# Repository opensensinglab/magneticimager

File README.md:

Magnetic Imaging Tile
======

Work-in-progress.  Please use at your own risk. <br>

This is a board intended to function as a "magnetic field camera", and visualize magnetic fields. 

### Version 3.0

The major advancement of v3.0 is a dramatic increase in the speed with which the tile data can be read out.  I have achieved ~2000 frames per second (fps), which allows visualizing even quickly varying fields (e.g. those in a 60Hz transformer, or a moving motor), but it's likely that the tile can achieve even higher framerates.  Version 3.0 reduces the size of the tile to an 8x8 grid of hall effect sensors (64 total), arrayed in a 4mm grid.  The boards should also still be tile-able, with up to 4 of the boards tileable with minimal borders to create a 16x16 array. 

For more information (and a video of the v3.0 tile in use), please see: 
https://hackaday.io/project/18518-iteration-8/log/91551-a-third-high-speed-magnetic-imager-tile-draft

### Version 2.0

Version 2.0 consists of an array of 12x12 hall effect sensors (144 total) that sense magnetic fields, arrayed in a 4mm grid.  Each sensor is connected to an array of analog switches, that allow an individual sensor to be addressed.  Read out is accomplished one magnetic "pixel" at a time, selecting a given hall sensor from the array, reading it's value (either using the internal ADC, or an external ADC), and repeating this process until the entire array has been read out.  

The current array is designed to be tile-able, with up to four of the boards (24x24 magnetic field sensors) arrayed together. 

The Arduino firmware has a framerate of approximately 10 frames per second, when the image data is streamed over the serial port and displayed using the Processing visualization.  The Raspberry Pi Python example achieves approximately 30fps.  The array itself is likely capable of much higher speeds, but one of the major limiting factors is currently the speed of the I2C I/O multiplexer (used to select which magnetometer to read from). 

For more information (and a video of the v2.0 tile in use), please see: 
https://hackaday.io/project/18518-iteration-8/log/64376-a-magnetic-imager-tile

# Open Source

This project is open source software and hardware, and is released under various open licenses.

# Disclaimer

**DISCLAIMER OF WARRANTIES AND LIMITATION OF LIABILITY.**

UNLESS OTHERWISE SEPARATELY UNDERTAKEN BY THE LICENSOR, TO THE EXTENT POSSIBLE, THE LICENSOR OFFERS THE LICENSED MATERIAL AS-IS AND AS-AVAILABLE, AND MAKES NO REPRESENTATIONS OR WARRANTIES OF ANY KIND CONCERNING THE LICENSED MATERIAL, WHETHER EXPRESS, IMPLIED, STATUTORY, OR OTHER. THIS INCLUDES, WITHOUT LIMITATION, WARRANTIES OF TITLE, MERCHANTABILITY, FITNESS FOR A PARTICULAR PURPOSE, NON-INFRINGEMENT, ABSENCE OF LATENT OR OTHER DEFECTS, ACCURACY, OR THE PRESENCE OR ABSENCE OF ERRORS, WHETHER OR NOT KNOWN OR DISCOVERABLE. WHERE DISCLAIMERS OF WARRANTIES ARE NOT ALLOWED IN FULL OR IN PART, THIS DISCLAIMER MAY NOT APPLY TO YOU.

TO THE EXTENT POSSIBLE, IN NO EVENT WILL THE LICENSOR BE LIABLE TO YOU ON ANY LEGAL THEORY (INCLUDING, WITHOUT LIMITATION, NEGLIGENCE) OR OTHERWISE FOR ANY DIRECT, SPECIAL, INDIRECT, INCIDENTAL, CONSEQUENTIAL, PUNITIVE, EXEMPLARY, OR OTHER LOSSES, COSTS, EXPENSES, OR DAMAGES ARISING OUT OF THIS PUBLIC LICENSE OR USE OF THE LICENSED MATERIAL, EVEN IF THE LICENSOR HAS BEEN ADVISED OF THE POSSIBILITY OF SUCH LOSSES, COSTS, EXPENSES, OR DAMAGES. WHERE A LIMITATION OF LIABILITY IS NOT ALLOWED IN FULL OR IN PART, THIS LIMITATION MAY NOT APPLY TO YOU.

THE DISCLAIMER OF WARRANTIES AND LIMITATION OF LIABILITY PROVIDED ABOVE SHALL BE INTERPRETED IN A MANNER THAT, TO THE EXTENT POSSIBLE, MOST CLOSELY APPROXIMATES AN ABSOLUTE DISCLAIMER AND WAIVER OF ALL LIABILITY.

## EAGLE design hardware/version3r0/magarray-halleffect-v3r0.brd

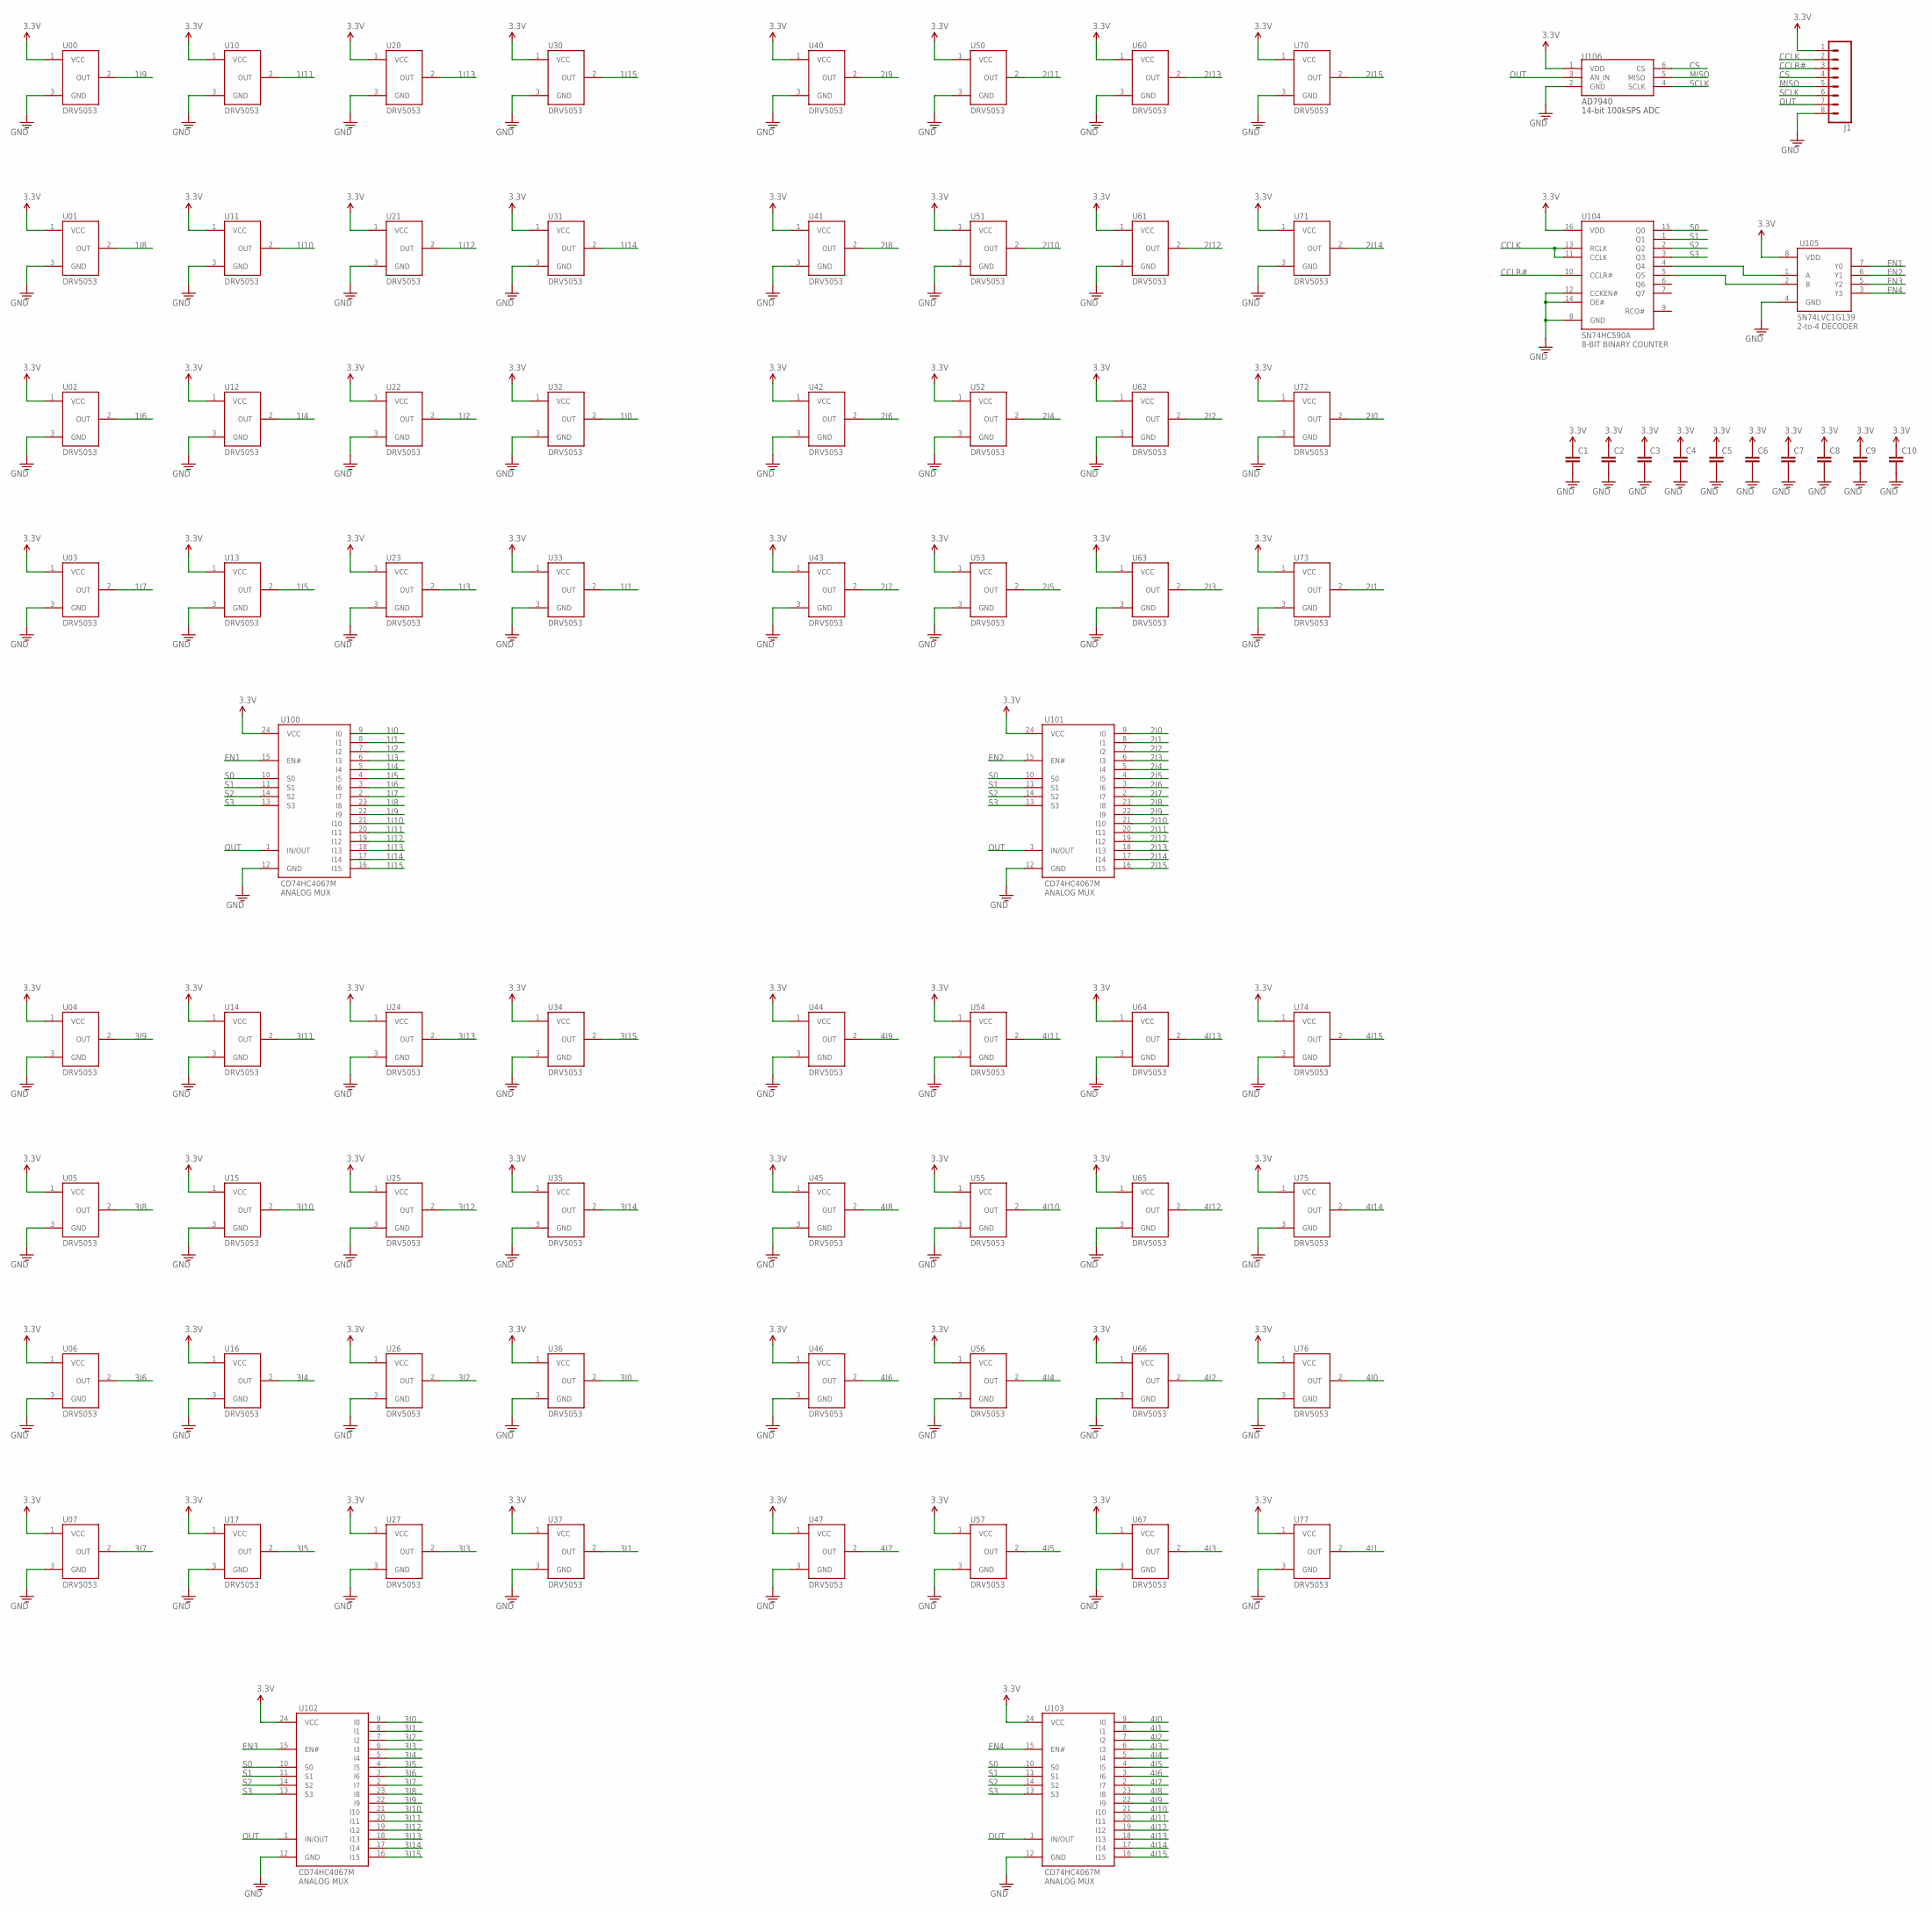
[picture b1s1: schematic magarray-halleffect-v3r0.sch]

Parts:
C1, C2, C3, C4, C5, C6, C7, C8, C9, C10: CAP0603; 0603
J1: CONN_08LOCK_NO_SILK; 1X08_LOCK_NO_SILK
U00, U01, U02, U03, U04, U05, U06, U07, U10, U11, U12, U13, U14, U15, U16, U17, U20, U21, U22, U23, U24, U25, U26, U27, U30, U31, U32, U33, U34, U35, U36, U37, U40, U41, U42, U43, U44, U45, U46, U47, U50, U51, U52, U53, U54, U55, U56, U57, U60, U61, U62, U63, U64, U65, U66, U67, U70, U71, U72, U73, U74, U75, U76, U77: DRV5053; SOT-23
U100, U101, U102, U103: CD74HC4067M; SOIC-24
U104: SN74HC509A; SO16
U105: SN74LVC1G139; SM8
U106: AD7940; SOT-23-6L

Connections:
1I0: U32.2 (OUT), U100.9 (I0)
1I1: U33.2 (OUT), U100.8 (I1)
1I2: U22.2 (OUT), U100.7 (I2)
1I3: U23.2 (OUT), U100.6 (I3)
1I4: U12.2 (OUT), U100.5 (I4)
1I5: U13.2 (OUT), U100.4 (I5)
1I6: U02.2 (OUT), U100.3 (I6)
1I7: U03.2 (OUT), U100.2 (I7)
1I8: U01.2 (OUT), U100.23 (I8)
1I9: U00.2 (OUT), U100.22 (I9)
1I10: U11.2 (OUT), U100.21 (I10)
1I11: U10.2 (OUT), U100.20 (I11)
1I12: U21.2 (OUT), U100.19 (I12)
1I13: U20.2 (OUT), U100.18 (I13)
1I14: U31.2 (OUT), U100.17 (I14)
1I15: U30.2 (OUT), U100.16 (I15)
2I0: U72.2 (OUT), U101.9 (I0)
2I1: U73.2 (OUT), U101.8 (I1)
2I2: U62.2 (OUT), U101.7 (I2)
2I3: U63.2 (OUT), U101.6 (I3)
2I4: U52.2 (OUT), U101.5 (I4)
2I5: U53.2 (OUT), U101.4 (I5)
2I6: U42.2 (OUT), U101.3 (I6)
2I7: U43.2 (OUT), U101.2 (I7)
2I8: U41.2 (OUT), U101.23 (I8)
2I9: U40.2 (OUT), U101.22 (I9)
2I10: U51.2 (OUT), U101.21 (I10)
2I11: U50.2 (OUT), U101.20 (I11)
2I12: U61.2 (OUT), U101.19 (I12)
2I13: U60.2 (OUT), U101.18 (I13)
2I14: U71.2 (OUT), U101.17 (I14)
2I15: U70.2 (OUT), U101.16 (I15)
3.3V: C1.1, C2.1, C3.1, C4.1, C5.1, C6.1, C7.1, C8.1, C9.1, C10.1, J1.1, U00.1 (VCC), U01.1 (VCC), U02.1 (VCC), U03.1 (VCC), U04.1 (VCC), U05.1 (VCC), U06.1 (VCC), U07.1 (VCC), U10.1 (VCC), U11.1 (VCC), U12.1 (VCC), U13.1 (VCC), U14.1 (VCC), U15.1 (VCC), U16.1 (VCC), U17.1 (VCC), U20.1 (VCC), U21.1 (VCC), U22.1 (VCC), U23.1 (VCC), U24.1 (VCC), U25.1 (VCC), U26.1 (VCC), U27.1 (VCC), U30.1 (VCC), U31.1 (VCC), U32.1 (VCC), U33.1 (VCC), U34.1 (VCC), U35.1 (VCC), U36.1 (VCC), U37.1 (VCC), U40.1 (VCC), U41.1 (VCC), U42.1 (VCC), U43.1 (VCC), U44.1 (VCC), U45.1 (VCC), U46.1 (VCC), U47.1 (VCC), U50.1 (VCC), U51.1 (VCC), U52.1 (VCC), U53.1 (VCC), U54.1 (VCC), U55.1 (VCC), U56.1 (VCC), U57.1 (VCC), U60.1 (VCC), U61.1 (VCC), U62.1 (VCC), U63.1 (VCC), U64.1 (VCC), U65.1 (VCC), U66.1 (VCC), U67.1 (VCC), U70.1 (VCC), U71.1 (VCC), U72.1 (VCC), U73.1 (VCC), U74.1 (VCC), U75.1 (VCC), U76.1 (VCC), U77.1 (VCC), U100.24 (VCC), U101.24 (VCC), U102.24 (VCC), U103.24 (VCC), U104.16 (VDD), U105.8 (VDD), U106.1 (VDD)
3I0: U36.2 (OUT), U102.9 (I0)
3I1: U37.2 (OUT), U102.8 (I1)
3I2: U26.2 (OUT), U102.7 (I2)
3I3: U27.2 (OUT), U102.6 (I3)
3I4: U16.2 (OUT), U102.5 (I4)
3I5: U17.2 (OUT), U102.4 (I5)
3I6: U06.2 (OUT), U102.3 (I6)
3I7: U07.2 (OUT), U102.2 (I7)
3I8: U05.2 (OUT), U102.23 (I8)
3I9: U04.2 (OUT), U102.22 (I9)
3I10: U15.2 (OUT), U102.21 (I10)
3I11: U14.2 (OUT), U102.20 (I11)
3I12: U25.2 (OUT), U102.19 (I12)
3I13: U24.2 (OUT), U102.18 (I13)
3I14: U35.2 (OUT), U102.17 (I14)
3I15: U34.2 (OUT), U102.16 (I15)
4I0: U76.2 (OUT), U103.9 (I0)
4I1: U77.2 (OUT), U103.8 (I1)
4I2: U66.2 (OUT), U103.7 (I2)
4I3: U67.2 (OUT), U103.6 (I3)
4I4: U56.2 (OUT), U103.5 (I4)
4I5: U57.2 (OUT), U103.4 (I5)
4I6: U46.2 (OUT), U103.3 (I6)
4I7: U47.2 (OUT), U103.2 (I7)
4I8: U45.2 (OUT), U103.23 (I8)
4I9: U44.2 (OUT), U103.22 (I9)
4I10: U55.2 (OUT), U103.21 (I10)
4I11: U54.2 (OUT), U103.20 (I11)
4I12: U65.2 (OUT), U103.19 (I12)
4I13: U64.2 (OUT), U103.18 (I13)
4I14: U75.2 (OUT), U103.17 (I14)
4I15: U74.2 (OUT), U103.16 (I15)
CCLK: J1.2, U104.11 (CCLK), U104.13 (RCLK)
CCLR#: J1.3, U104.10 (CCLR#)
CS: J1.4, U106.6 (CS)
EN1: U100.15 (EN#), U105.7 (Y0)
EN2: U101.15 (EN#), U105.6 (Y1)
EN3: U102.15 (EN#), U105.5 (Y2)
EN4: U103.15 (EN#), U105.3 (Y3)
GND: C1.2, C2.2, C3.2, C4.2, C5.2, C6.2, C7.2, C8.2, C9.2, C10.2, J1.8, U00.3 (GND), U01.3 (GND), U02.3 (GND), U03.3 (GND), U04.3 (GND), U05.3 (GND), U06.3 (GND), U07.3 (GND), U10.3 (GND), U11.3 (GND), U12.3 (GND), U13.3 (GND), U14.3 (GND), U15.3 (GND), U16.3 (GND), U17.3 (GND), U20.3 (GND), U21.3 (GND), U22.3 (GND), U23.3 (GND), U24.3 (GND), U25.3 (GND), U26.3 (GND), U27.3 (GND), U30.3 (GND), U31.3 (GND), U32.3 (GND), U33.3 (GND), U34.3 (GND), U35.3 (GND), U36.3 (GND), U37.3 (GND), U40.3 (GND), U41.3 (GND), U42.3 (GND), U43.3 (GND), U44.3 (GND), U45.3 (GND), U46.3 (GND), U47.3 (GND), U50.3 (GND), U51.3 (GND), U52.3 (GND), U53.3 (GND), U54.3 (GND), U55.3 (GND), U56.3 (GND), U57.3 (GND), U60.3 (GND), U61.3 (GND), U62.3 (GND), U63.3 (GND), U64.3 (GND), U65.3 (GND), U66.3 (GND), U67.3 (GND), U70.3 (GND), U71.3 (GND), U72.3 (GND), U73.3 (GND), U74.3 (GND), U75.3 (GND), U76.3 (GND), U77.3 (GND), U100.12 (GND), U101.12 (GND), U102.12 (GND), U103.12 (GND), U104.8 (GND), U104.12 (CCKEN#), U104.14 (OE#), U105.4 (GND), U106.2 (GND)
MISO: J1.5, U106.5 (MISO)
unnamed: U104.4 (Q4), U105.1 (A)
unnamed: U104.5 (Q5), U105.2 (B)
OUT: J1.7, U100.1 (IN/OUT), U101.1 (IN/OUT), U102.1 (IN/OUT), U103.1 (IN/OUT), U106.3 (AN_IN)
S0: U100.10 (S0), U101.10 (S0), U102.10 (S0), U103.10 (S0), U104.15 (Q0)
S1: U100.11 (S1), U101.11 (S1), U102.11 (S1), U103.11 (S1), U104.1 (Q1)
S2: U100.14 (S2), U101.14 (S2), U102.14 (S2), U103.14 (S2), U104.2 (Q2)
S3: U100.13 (S3), U101.13 (S3), U102.13 (S3), U103.13 (S3), U104.3 (Q3)
SCLK: J1.6, U106.4 (SCLK)

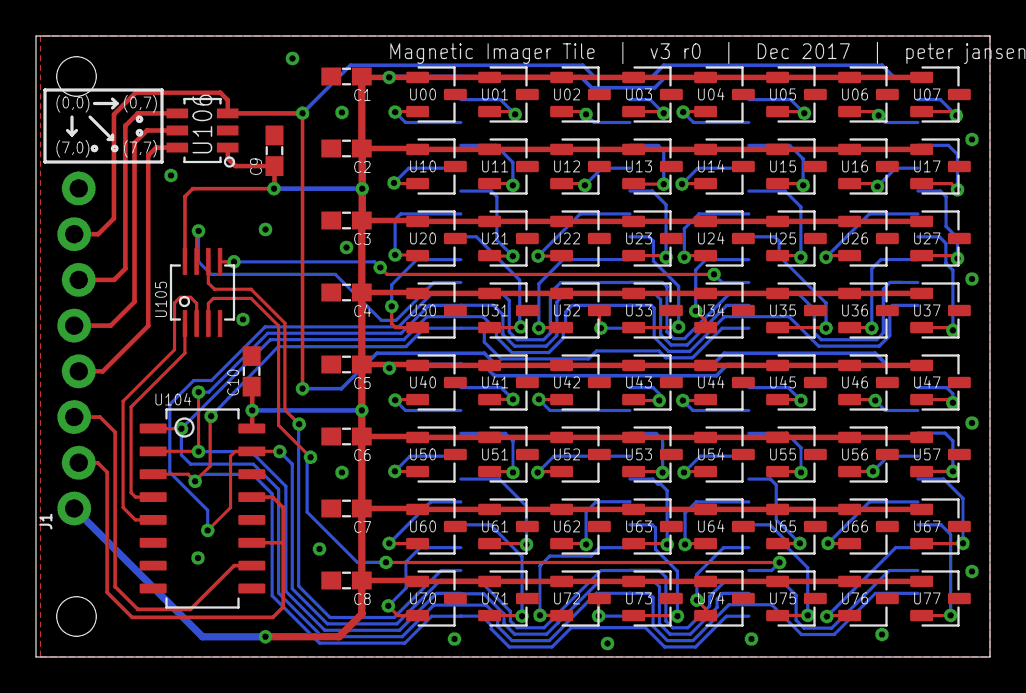
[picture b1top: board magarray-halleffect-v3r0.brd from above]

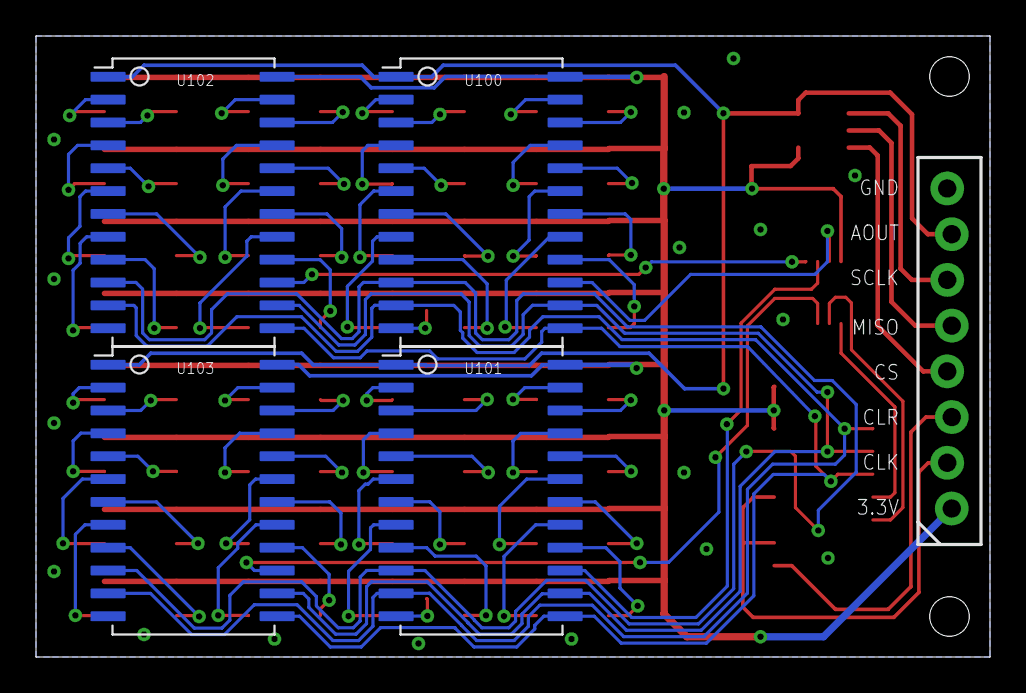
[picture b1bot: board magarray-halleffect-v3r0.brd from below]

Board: 2 copper layers, 53.0 x 34.5 mm, 82 parts (4 on the bottom side), 82 nets.

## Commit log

2017-07-29 Added readme, license
2017-07-29 added v2r0 hardware
2017-07-29 Added python example for raspberry pi
2017-07-29 Added Arduino and Processing code
2017-07-29 added errata for v2r0
2017-07-29 minor changes
2017-12-31 Added v3r0 imager tile, a smaller 8x8 version of v2, with a binary counter incrementing interface
2018-02-12 added schematic
2018-02-12 Added v3 code
2018-02-12 readme update
2019-09-13 Added Python/Raspberry Pi example for magnetic tile version 3

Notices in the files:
parts and their libraries:
SparkFun-Connectors: Licensing: Creative Commons ShareAlike 4.0 International - https://creativecommons.org/licenses/by-sa/4.0
